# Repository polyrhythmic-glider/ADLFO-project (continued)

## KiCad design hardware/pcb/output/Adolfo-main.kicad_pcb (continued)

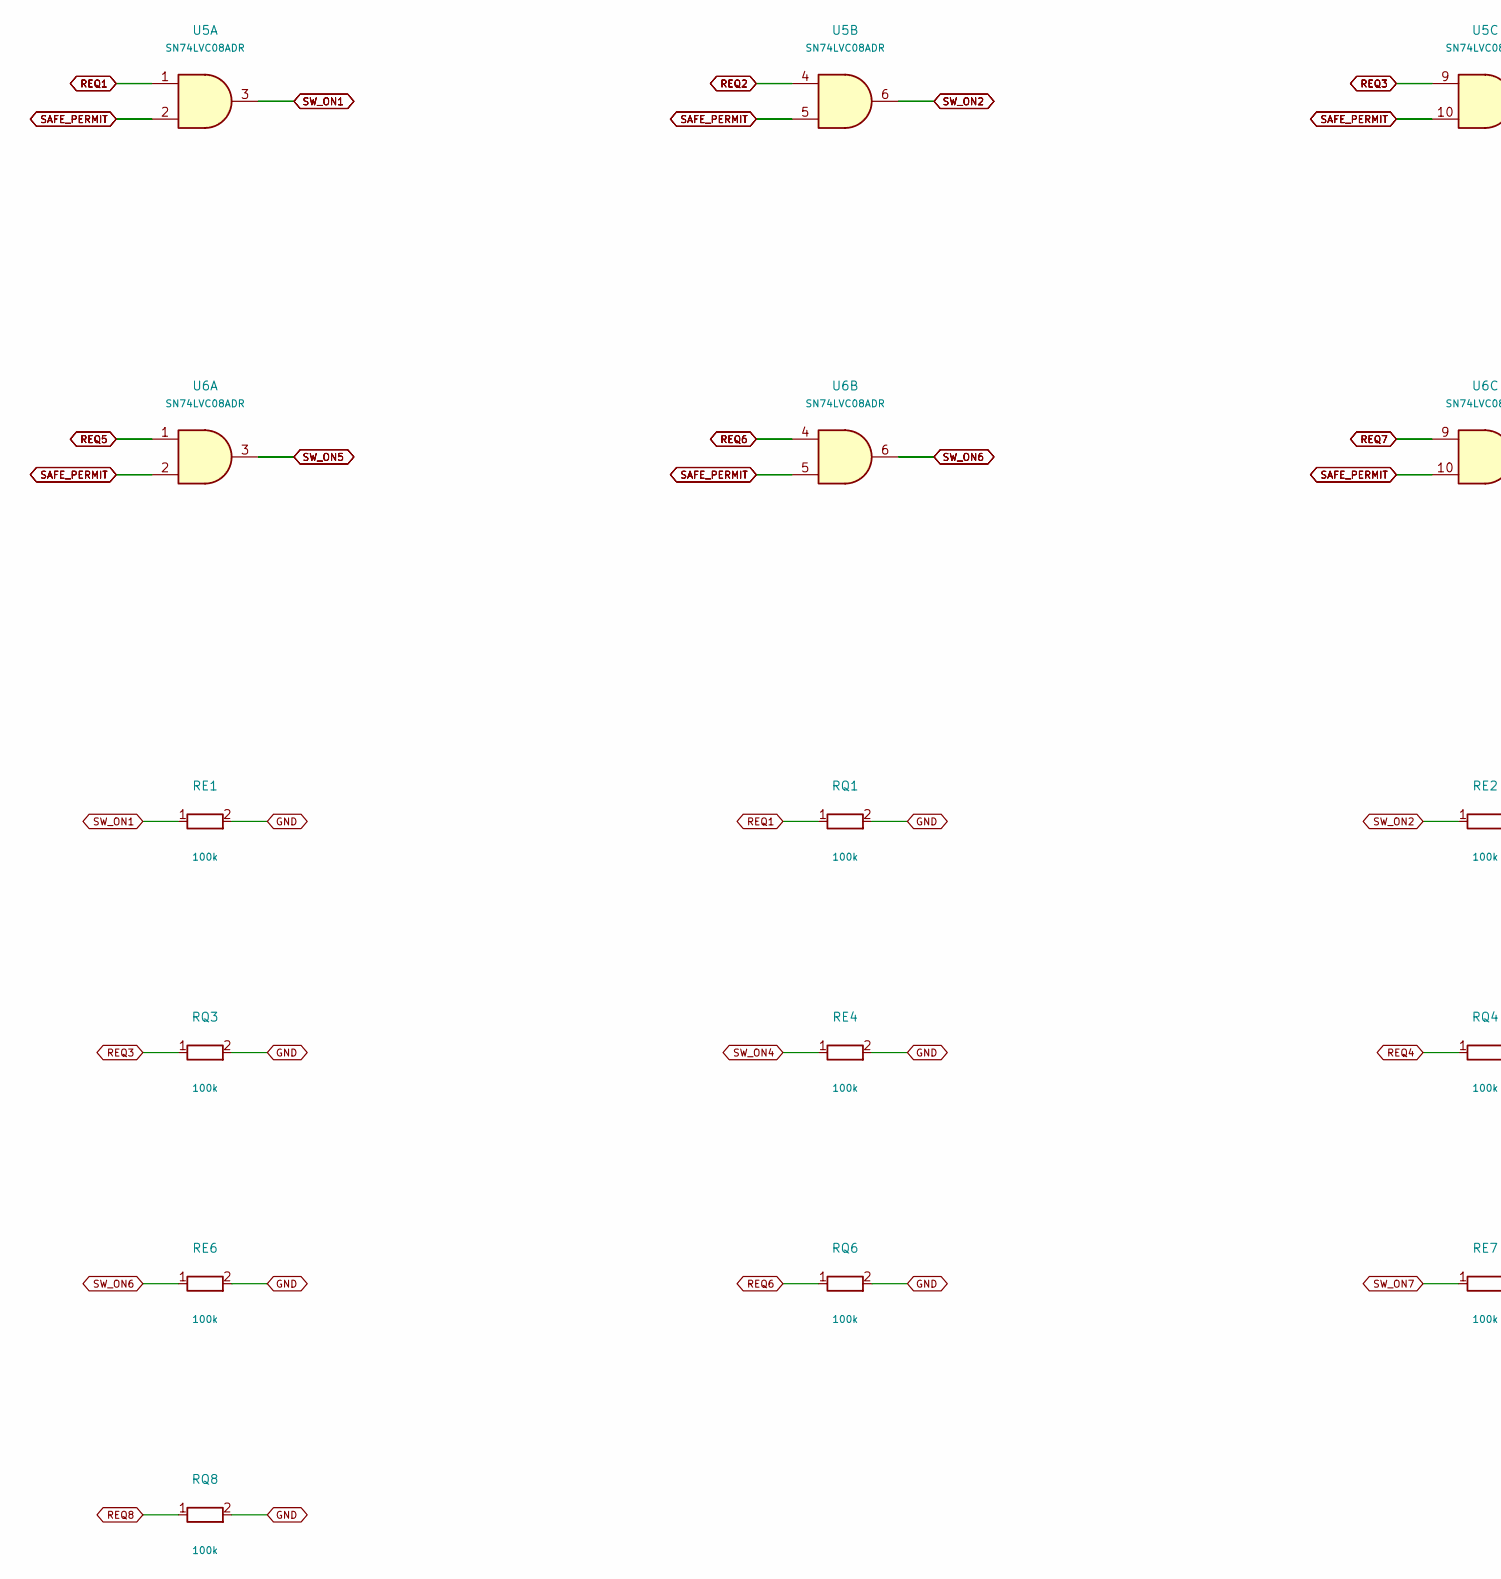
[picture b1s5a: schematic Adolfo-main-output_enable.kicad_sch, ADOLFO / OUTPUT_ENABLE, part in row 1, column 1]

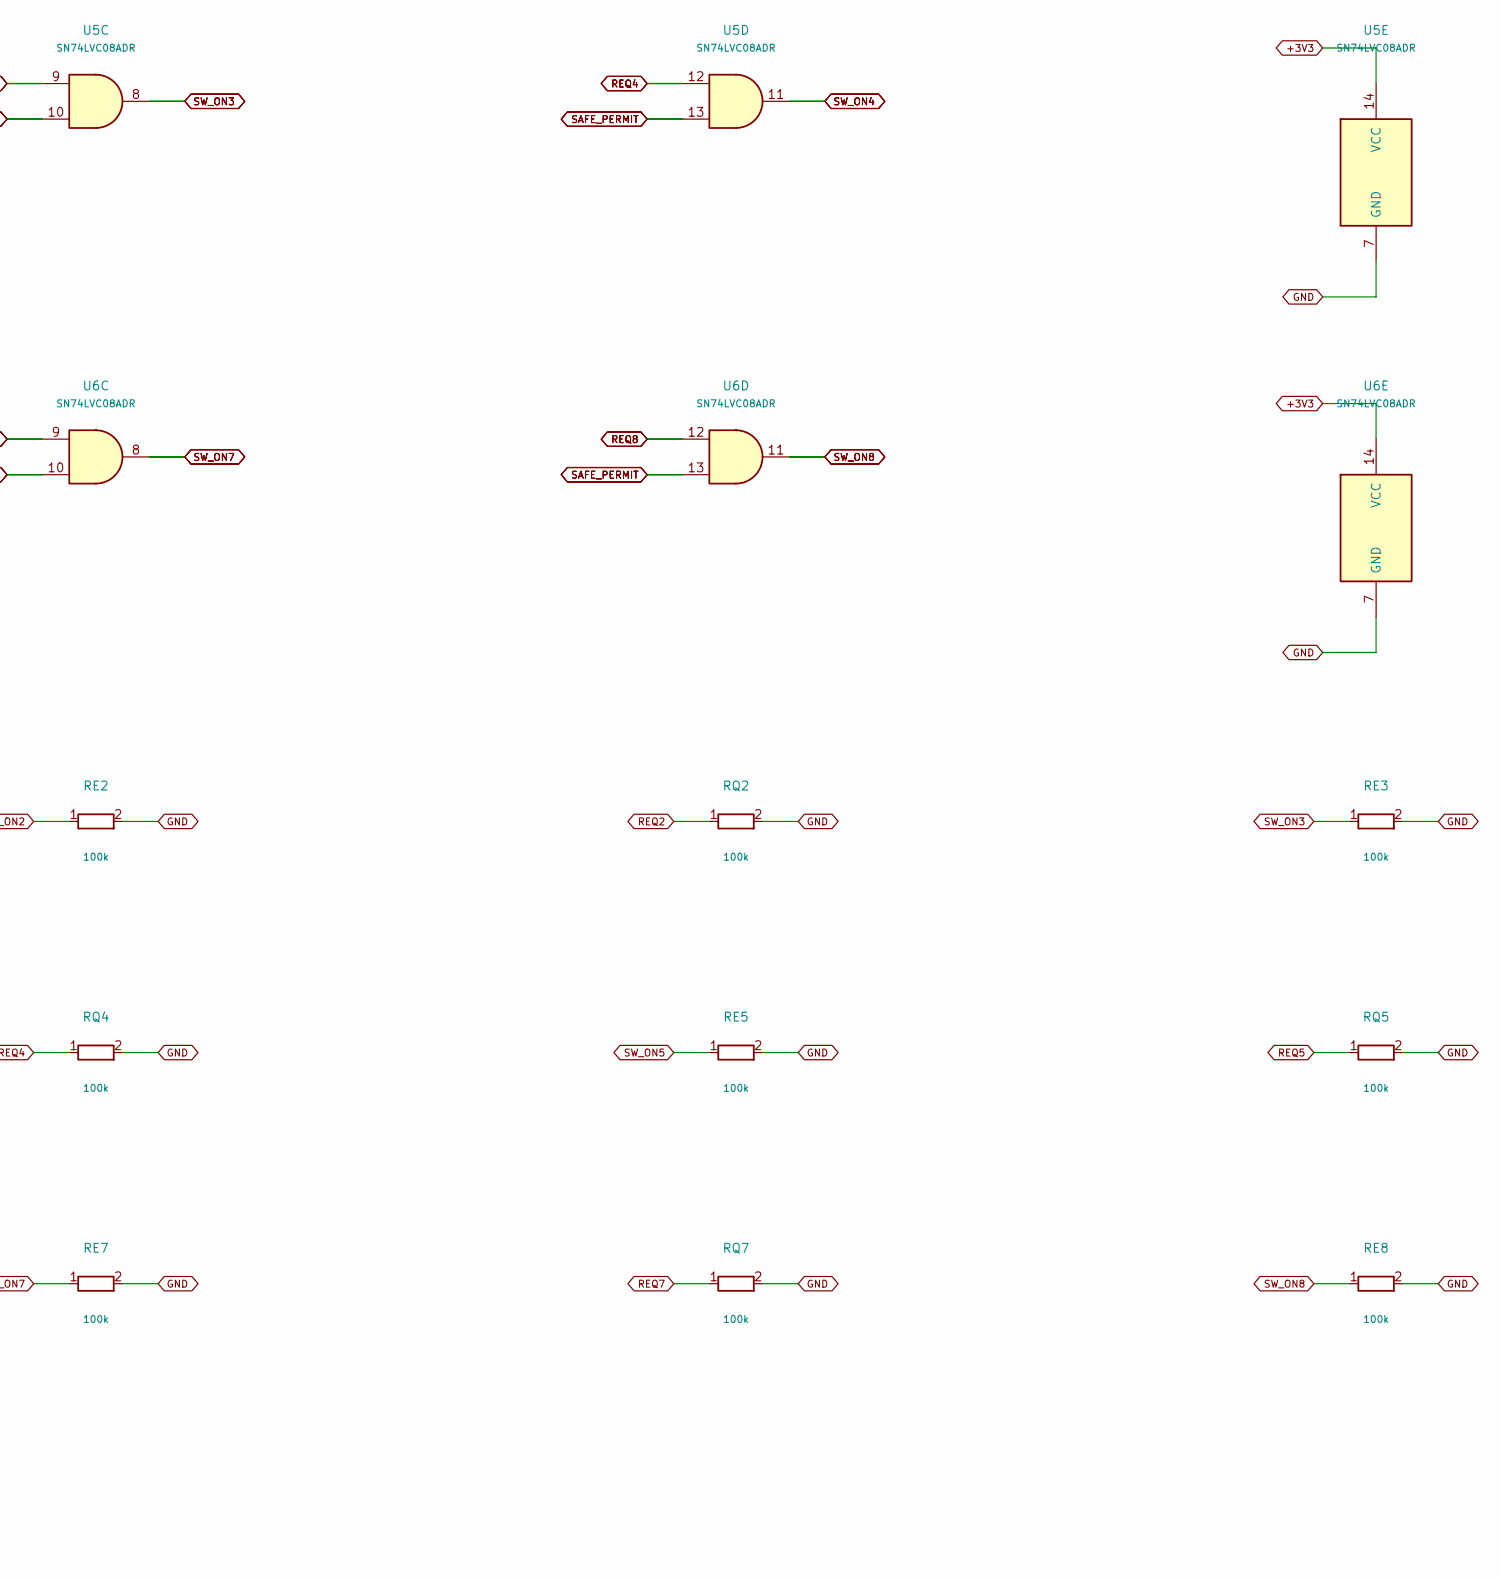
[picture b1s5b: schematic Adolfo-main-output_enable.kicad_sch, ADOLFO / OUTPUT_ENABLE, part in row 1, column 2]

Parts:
RE1, RE2, RE3, RE4, RE5, RE6, RE7, RE8: 100k; r0805
RQ1, RQ2, RQ3, RQ4, RQ5, RQ6, RQ7, RQ8: 100k; r0805
U5, U6: SN74LVC08ADR; soic14; MPN SN74LVC08ADR

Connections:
+3V3: U5.14 (VCC), U6.14 (VCC); also elsewhere on the board
GND: RE1.2, RE2.2, RE3.2, RE4.2, RE5.2, RE6.2, RE7.2, RE8.2, RQ1.2, RQ2.2, RQ3.2, RQ4.2, RQ5.2, RQ6.2, RQ7.2, RQ8.2, U5.7 (GND), U6.7 (GND); also elsewhere on the board
REQ1: RQ1.1, U5.1; also elsewhere on the board
REQ2: RQ2.1, U5.4; also elsewhere on the board
REQ3: RQ3.1, U5.9; also elsewhere on the board
REQ4: RQ4.1, U5.12; also elsewhere on the board
REQ5: RQ5.1, U6.1; also elsewhere on the board
REQ6: RQ6.1, U6.4; also elsewhere on the board
REQ7: RQ7.1, U6.9; also elsewhere on the board
REQ8: RQ8.1, U6.12; also elsewhere on the board
SAFE_PERMIT: U5.2, U5.5, U5.10, U5.13, U6.2, U6.5, U6.10, U6.13; also elsewhere on the board
SW_ON1: RE1.1, U5.3; also elsewhere on the board
SW_ON2: RE2.1, U5.6; also elsewhere on the board
SW_ON3: RE3.1, U5.8; also elsewhere on the board
SW_ON4: RE4.1, U5.11; also elsewhere on the board
SW_ON5: RE5.1, U6.3; also elsewhere on the board
SW_ON6: RE6.1, U6.6; also elsewhere on the board
SW_ON7: RE7.1, U6.8; also elsewhere on the board
SW_ON8: RE8.1, U6.11; also elsewhere on the board

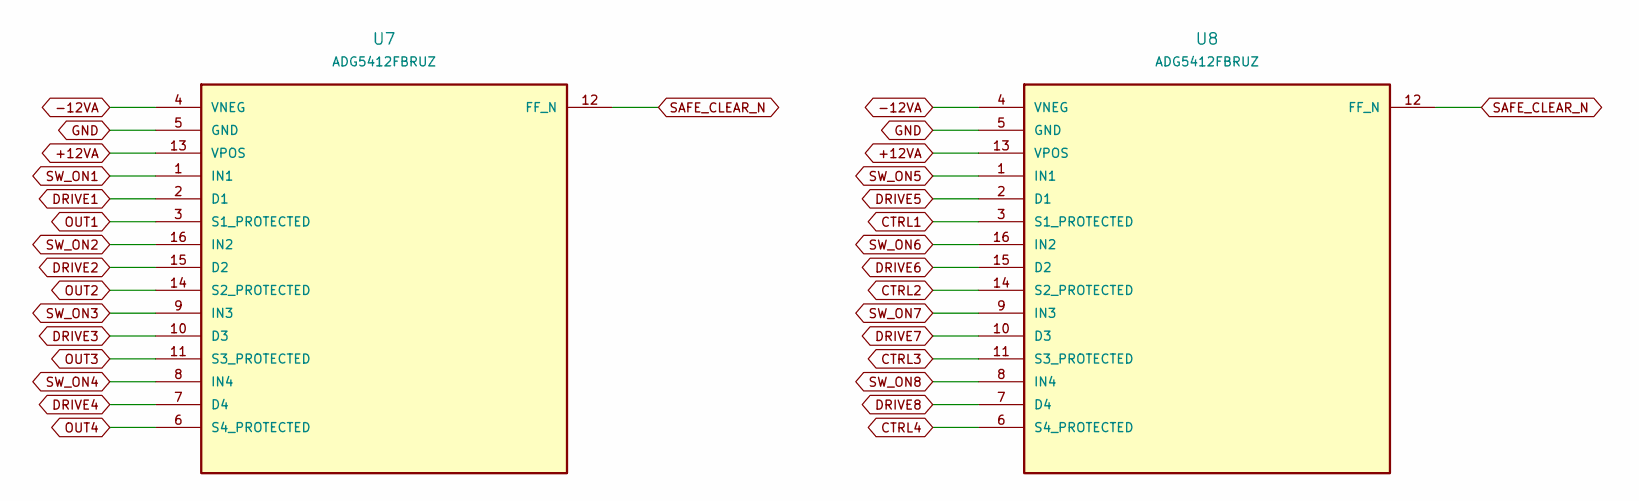
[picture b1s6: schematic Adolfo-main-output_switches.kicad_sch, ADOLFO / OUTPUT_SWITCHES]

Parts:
U7, U8: ADG5412FBRUZ; tssop16; MPN ADG5412FBRUZ

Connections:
+12VA: U7.13 (VPOS), U8.13 (VPOS); also elsewhere on the board
-12VA: U7.4 (VNEG), U8.4 (VNEG); also elsewhere on the board
CTRL1: U8.3 (S1_PROTECTED); also elsewhere on the board
CTRL2: U8.14 (S2_PROTECTED); also elsewhere on the board
CTRL3: U8.11 (S3_PROTECTED); also elsewhere on the board
CTRL4: U8.6 (S4_PROTECTED); also elsewhere on the board
DRIVE1: U7.2 (D1); also elsewhere on the board
DRIVE2: U7.15 (D2); also elsewhere on the board
DRIVE3: U7.10 (D3); also elsewhere on the board
DRIVE4: U7.7 (D4); also elsewhere on the board
DRIVE5: U8.2 (D1); also elsewhere on the board
DRIVE6: U8.15 (D2); also elsewhere on the board
DRIVE7: U8.10 (D3); also elsewhere on the board
DRIVE8: U8.7 (D4); also elsewhere on the board
GND: U7.5 (GND), U8.5 (GND); also elsewhere on the board
OUT1: U7.3 (S1_PROTECTED); also elsewhere on the board
OUT2: U7.14 (S2_PROTECTED); also elsewhere on the board
OUT3: U7.11 (S3_PROTECTED); also elsewhere on the board
OUT4: U7.6 (S4_PROTECTED); also elsewhere on the board
SAFE_CLEAR_N: U7.12 (FF_N), U8.12 (FF_N); also elsewhere on the board
SW_ON1: U7.1 (IN1); also elsewhere on the board
SW_ON2: U7.16 (IN2); also elsewhere on the board
SW_ON3: U7.9 (IN3); also elsewhere on the board
SW_ON4: U7.8 (IN4); also elsewhere on the board
SW_ON5: U8.1 (IN1); also elsewhere on the board
SW_ON6: U8.16 (IN2); also elsewhere on the board
SW_ON7: U8.9 (IN3); also elsewhere on the board
SW_ON8: U8.8 (IN4); also elsewhere on the board

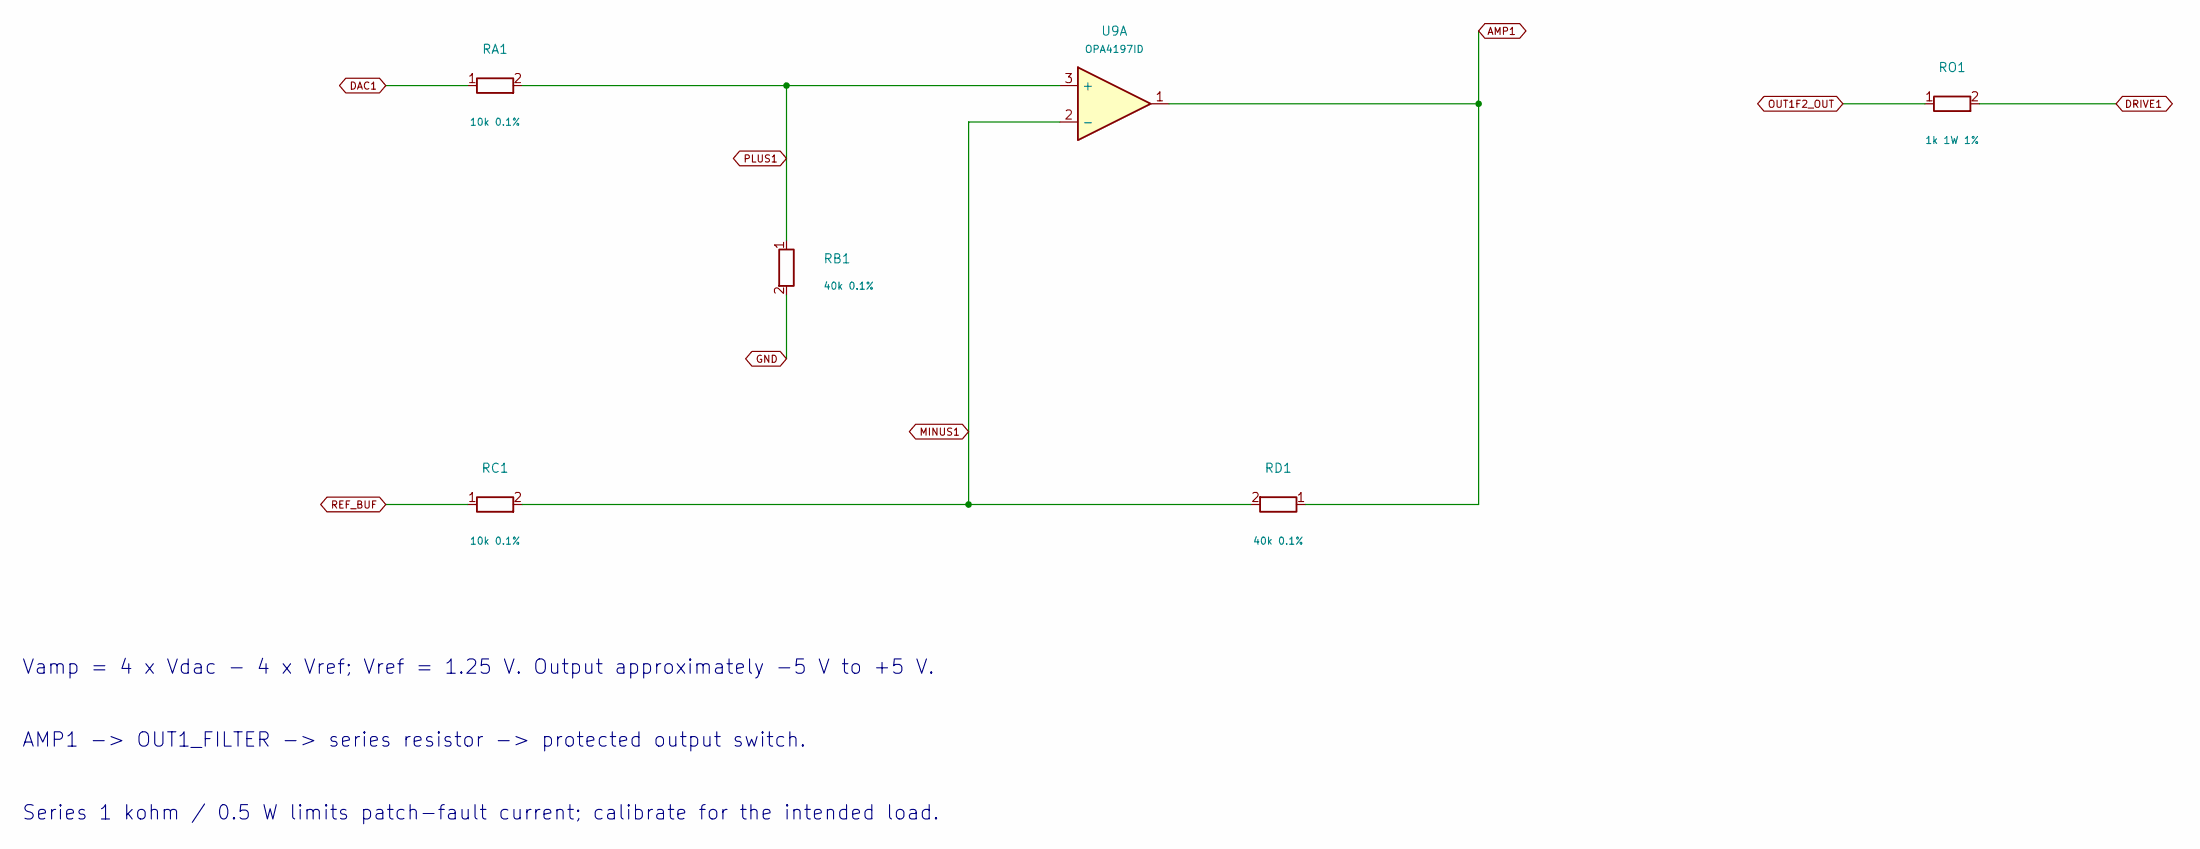
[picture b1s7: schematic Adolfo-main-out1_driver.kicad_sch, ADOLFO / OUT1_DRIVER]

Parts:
RA1: 10k 0.1%; r0805
RB1: 40k 0.1%; r0805
RC1: 10k 0.1%; r0805
RD1: 40k 0.1%; r0805
RO1: 1k 1W 1%; r2010; MPN CRCW20101K00FKEFHP
U9: OPA4197ID; soic14; MPN OPA4197ID

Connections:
AMP1: RD1.1, U9.1; also elsewhere on the board
DAC1: RA1.1; also elsewhere on the board
DRIVE1: RO1.2; also elsewhere on the board
GND: RB1.2; also elsewhere on the board
MINUS1: RC1.2, RD1.2, U9.2 (-)
OUT1F2_OUT: RO1.1; also elsewhere on the board
PLUS1: RA1.2, RB1.1, U9.3 (+)
REF_BUF: RC1.1; also elsewhere on the board

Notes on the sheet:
AMP1 -> OUT1_FILTER -> series resistor -> protected output switch.
Vamp = 4 x Vdac - 4 x Vref; Vref = 1.25 V. Output approximately -5 V to +5 V.
Series 1 kohm / 0.5 W limits patch-fault current; calibrate for the intended load.

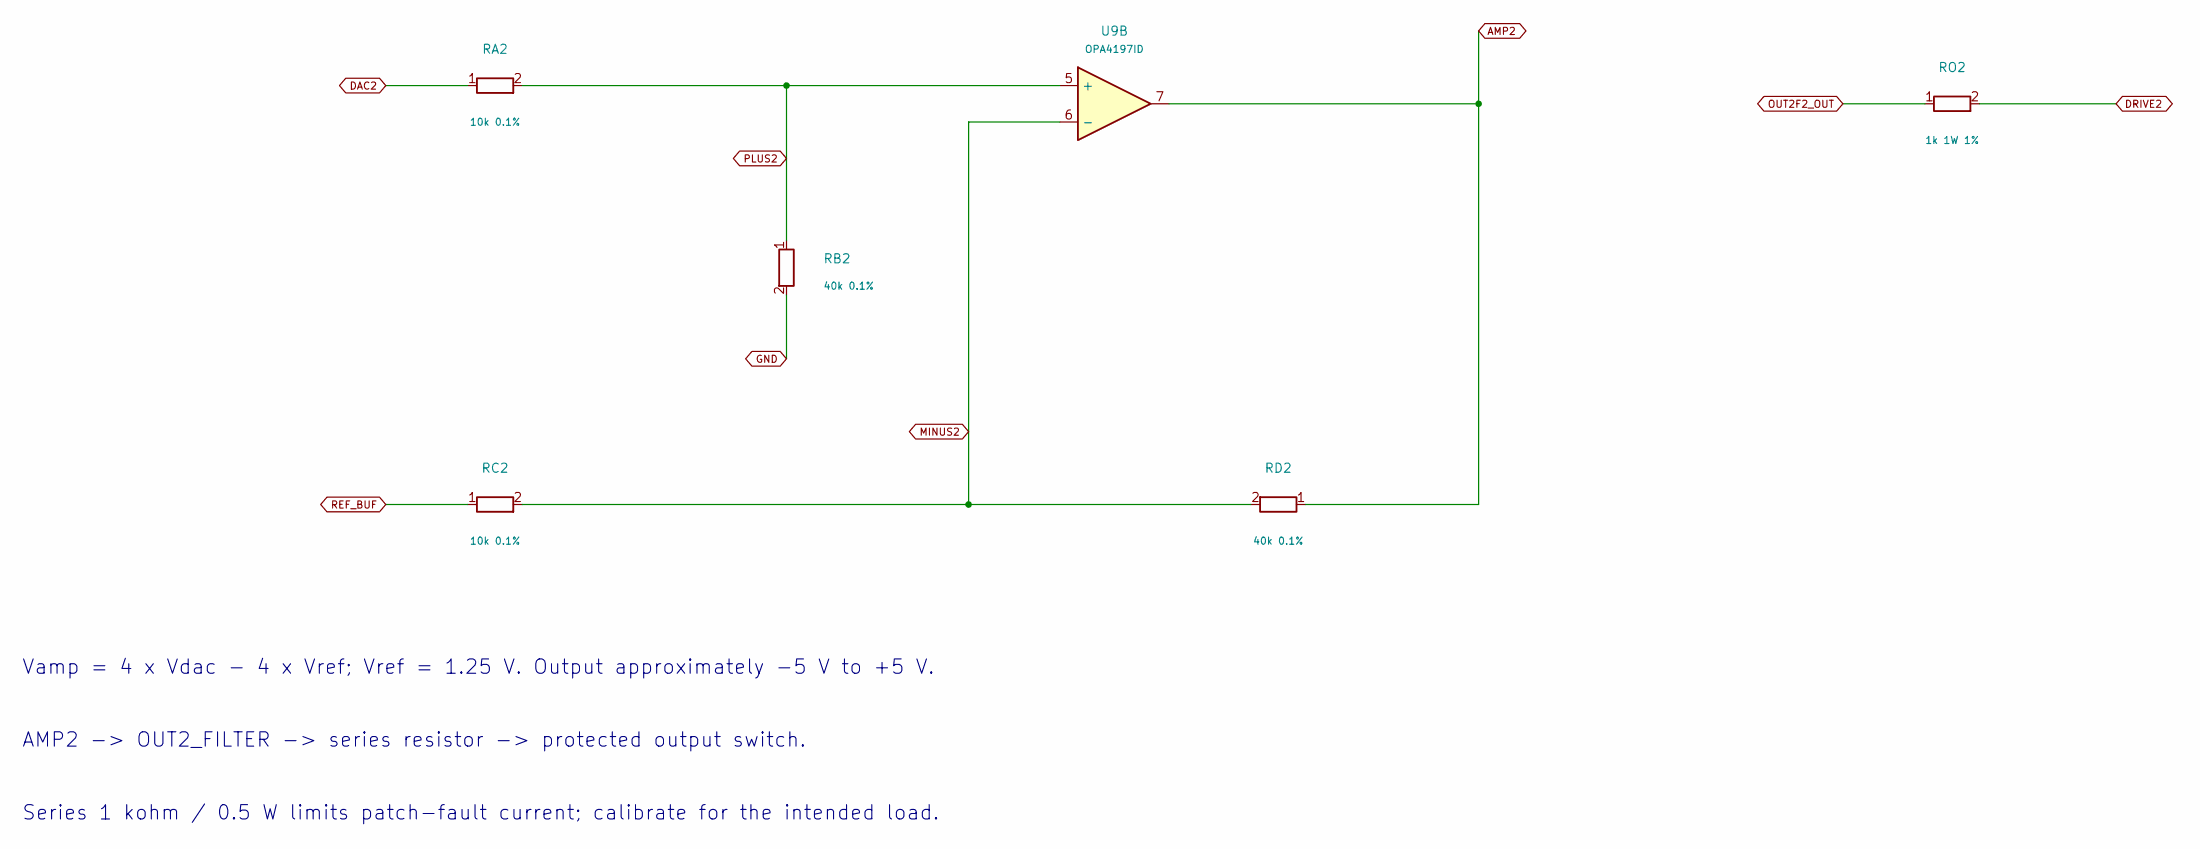
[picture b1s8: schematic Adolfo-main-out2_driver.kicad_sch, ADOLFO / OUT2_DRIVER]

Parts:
RA2: 10k 0.1%; r0805
RB2: 40k 0.1%; r0805
RC2: 10k 0.1%; r0805
RD2: 40k 0.1%; r0805
RO2: 1k 1W 1%; r2010; MPN CRCW20101K00FKEFHP
U9: OPA4197ID; soic14; MPN OPA4197ID

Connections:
AMP2: RD2.1, U9.7; also elsewhere on the board
DAC2: RA2.1; also elsewhere on the board
DRIVE2: RO2.2; also elsewhere on the board
GND: RB2.2; also elsewhere on the board
MINUS2: RC2.2, RD2.2, U9.6 (-)
OUT2F2_OUT: RO2.1; also elsewhere on the board
PLUS2: RA2.2, RB2.1, U9.5 (+)
REF_BUF: RC2.1; also elsewhere on the board

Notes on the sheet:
AMP2 -> OUT2_FILTER -> series resistor -> protected output switch.
Vamp = 4 x Vdac - 4 x Vref; Vref = 1.25 V. Output approximately -5 V to +5 V.
Series 1 kohm / 0.5 W limits patch-fault current; calibrate for the intended load.

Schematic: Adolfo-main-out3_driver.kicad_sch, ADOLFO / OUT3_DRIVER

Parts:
RA3: 10k 0.1%; r0805
RB3: 40k 0.1%; r0805
RC3: 10k 0.1%; r0805
RD3: 40k 0.1%; r0805
RO3: 1k 1W 1%; r2010; MPN CRCW20101K00FKEFHP
U9: OPA4197ID; soic14; MPN OPA4197ID

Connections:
AMP3: RD3.1, U9.8; also elsewhere on the board
DAC3: RA3.1; also elsewhere on the board
DRIVE3: RO3.2; also elsewhere on the board
GND: RB3.2; also elsewhere on the board
MINUS3: RC3.2, RD3.2, U9.9 (-)
OUT3F2_OUT: RO3.1; also elsewhere on the board
PLUS3: RA3.2, RB3.1, U9.10 (+)
REF_BUF: RC3.1; also elsewhere on the board

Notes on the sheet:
AMP3 -> OUT3_FILTER -> series resistor -> protected output switch.
Vamp = 4 x Vdac - 4 x Vref; Vref = 1.25 V. Output approximately -5 V to +5 V.
Series 1 kohm / 0.5 W limits patch-fault current; calibrate for the intended load.

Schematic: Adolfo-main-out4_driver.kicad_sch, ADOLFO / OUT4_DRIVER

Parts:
RA4: 10k 0.1%; r0805
RB4: 40k 0.1%; r0805
RC4: 10k 0.1%; r0805
RD4: 40k 0.1%; r0805
RO4: 1k 1W 1%; r2010; MPN CRCW20101K00FKEFHP
U9: OPA4197ID; soic14; MPN OPA4197ID

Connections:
AMP4: RD4.1, U9.14; also elsewhere on the board
DAC4: RA4.1; also elsewhere on the board
DRIVE4: RO4.2; also elsewhere on the board
GND: RB4.2; also elsewhere on the board
MINUS4: RC4.2, RD4.2, U9.13 (-)
OUT4F2_OUT: RO4.1; also elsewhere on the board
PLUS4: RA4.2, RB4.1, U9.12 (+)
REF_BUF: RC4.1; also elsewhere on the board

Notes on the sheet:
AMP4 -> OUT4_FILTER -> series resistor -> protected output switch.
Vamp = 4 x Vdac - 4 x Vref; Vref = 1.25 V. Output approximately -5 V to +5 V.
Series 1 kohm / 0.5 W limits patch-fault current; calibrate for the intended load.

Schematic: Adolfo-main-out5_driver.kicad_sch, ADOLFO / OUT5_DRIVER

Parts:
RA5: 10k 0.1%; r0805
RB5: 40k 0.1%; r0805
RC5: 10k 0.1%; r0805
RD5: 40k 0.1%; r0805
RO5: 1k 1W 1%; r2010; MPN CRCW20101K00FKEFHP
U10: OPA4197ID; soic14; MPN OPA4197ID

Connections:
AMP5: RD5.1, RO5.1, U10.1
DAC5: RA5.1; also elsewhere on the board
DRIVE5: RO5.2; also elsewhere on the board
GND: RB5.2; also elsewhere on the board
MINUS5: RC5.2, RD5.2, U10.2 (-)
PLUS5: RA5.2, RB5.1, U10.3 (+)
REF_BUF: RC5.1; also elsewhere on the board

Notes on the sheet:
Vamp = 4 x Vdac - 4 x Vref; Vref = 1.25 V. Output approximately -5 V to +5 V.
Series 1 kohm / 0.5 W limits patch-fault current; calibrate for the intended load.

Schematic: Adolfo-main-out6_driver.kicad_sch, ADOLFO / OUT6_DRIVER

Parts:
RA6: 10k 0.1%; r0805
RB6: 40k 0.1%; r0805
RC6: 10k 0.1%; r0805
RD6: 40k 0.1%; r0805
RO6: 1k 1W 1%; r2010; MPN CRCW20101K00FKEFHP
U10: OPA4197ID; soic14; MPN OPA4197ID

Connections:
AMP6: RD6.1, RO6.1, U10.7
DAC6: RA6.1; also elsewhere on the board
DRIVE6: RO6.2; also elsewhere on the board
GND: RB6.2; also elsewhere on the board
MINUS6: RC6.2, RD6.2, U10.6 (-)
PLUS6: RA6.2, RB6.1, U10.5 (+)
REF_BUF: RC6.1; also elsewhere on the board

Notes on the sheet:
Vamp = 4 x Vdac - 4 x Vref; Vref = 1.25 V. Output approximately -5 V to +5 V.
Series 1 kohm / 0.5 W limits patch-fault current; calibrate for the intended load.

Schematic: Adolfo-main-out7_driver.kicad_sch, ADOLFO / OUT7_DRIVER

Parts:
RA7: 10k 0.1%; r0805
RB7: 40k 0.1%; r0805
RC7: 10k 0.1%; r0805
RD7: 40k 0.1%; r0805
RO7: 1k 1W 1%; r2010; MPN CRCW20101K00FKEFHP
U10: OPA4197ID; soic14; MPN OPA4197ID

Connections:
AMP7: RD7.1, RO7.1, U10.8
DAC7: RA7.1; also elsewhere on the board
DRIVE7: RO7.2; also elsewhere on the board
GND: RB7.2; also elsewhere on the board
MINUS7: RC7.2, RD7.2, U10.9 (-)
PLUS7: RA7.2, RB7.1, U10.10 (+)
REF_BUF: RC7.1; also elsewhere on the board

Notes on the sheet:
Vamp = 4 x Vdac - 4 x Vref; Vref = 1.25 V. Output approximately -5 V to +5 V.
Series 1 kohm / 0.5 W limits patch-fault current; calibrate for the intended load.

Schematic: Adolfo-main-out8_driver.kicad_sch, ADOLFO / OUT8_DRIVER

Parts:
RA8: 10k 0.1%; r0805
RB8: 40k 0.1%; r0805
RC8: 10k 0.1%; r0805
RD8: 40k 0.1%; r0805
RO8: 1k 1W 1%; r2010; MPN CRCW20101K00FKEFHP
U10: OPA4197ID; soic14; MPN OPA4197ID

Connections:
AMP8: RD8.1, RO8.1, U10.14
DAC8: RA8.1; also elsewhere on the board
DRIVE8: RO8.2; also elsewhere on the board
GND: RB8.2; also elsewhere on the board
MINUS8: RC8.2, RD8.2, U10.13 (-)
PLUS8: RA8.2, RB8.1, U10.12 (+)
REF_BUF: RC8.1; also elsewhere on the board

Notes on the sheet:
Vamp = 4 x Vdac - 4 x Vref; Vref = 1.25 V. Output approximately -5 V to +5 V.
Series 1 kohm / 0.5 W limits patch-fault current; calibrate for the intended load.

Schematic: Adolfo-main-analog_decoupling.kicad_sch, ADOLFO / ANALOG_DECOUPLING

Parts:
U9, U10, U11, U21, U22, U23, U24: OPA4197ID; soic14; MPN OPA4197ID

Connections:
+12VA: U9.4 (V+), U10.4 (V+), U11.4 (V+), U21.4 (V+), U22.4 (V+), U23.4 (V+), U24.4 (V+); also elsewhere on the board
-12VA: U9.11 (V-), U10.11 (V-), U11.11 (V-), U21.11 (V-), U22.11 (V-), U23.11 (V-), U24.11 (V-); also elsewhere on the board

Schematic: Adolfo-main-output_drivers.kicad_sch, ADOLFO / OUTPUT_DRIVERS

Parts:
C1, C2, C3, C4, C5, C6: 100nF 50V; c0805

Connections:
+12VA: C1.1, C3.1, C5.1; also elsewhere on the board
-12VA: C2.1, C4.1, C6.1; also elsewhere on the board
GND: C1.2, C2.2, C3.2, C4.2, C5.2, C6.2; also elsewhere on the board

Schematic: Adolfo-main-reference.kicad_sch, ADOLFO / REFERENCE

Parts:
RREF1, RREF2: 10k 0.1%; r0805
U11: OPA4197ID; soic14; MPN OPA4197ID

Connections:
GND: RREF2.2, U11.5 (+), U11.10 (+), U11.12 (+); also elsewhere on the board
REF2V5: RREF1.1; also elsewhere on the board
REF_BUF: U11.1, U11.2 (-); also elsewhere on the board
REF_HALF: RREF1.2, RREF2.1, U11.3 (+)
UNUSED_FB7: U11.6 (-), U11.7
UNUSED_FB8: U11.8, U11.9 (-)
UNUSED_FB14: U11.13 (-), U11.14

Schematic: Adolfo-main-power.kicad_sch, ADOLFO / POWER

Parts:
C7: 47uF 10V; c0805
C8: 10uF 10V; c0805
C60, C61: 22uF 25V X7R; c1210
C62: 100nF 50V; c0805
C63: 100nF; c0805
CD1, CD2, CD3, CD4, CD5, CD6, CD7, CD8, CD9: 100nF; c0805
CI1, CI2, CI3, CI4: 100pF C0G; c0805
CI5, CI6, CI7, CI8: 1nF C0G; c0805
D1, D2: SS14; sma
F1: Littelfuse 1206L075/24YR; fuse1206
F2: Littelfuse 1206L025/30YR; fuse1206
FB1: BLM21PG601SN1D; r0805
J16: Wurth 61201021621 IDC10; idc10
RI1, RI2, RI3, RI4, RI5, RI6, RI7, RI8: 1k 1W 1%; r2010; MPN CRCW20101K00FKEFHP
TP1: GND; testpoint
TP2: +12VA; testpoint
TP3: -12VA; testpoint
TP4: +5D; testpoint
TP5: +5A; testpoint
TP6: REF_BUF; testpoint
U25: R-78E5.0-1.0; recom; MPN R-78E5.0-1.0

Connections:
+3V3: CD3.1, CD4.1, CD5.1; also elsewhere on the board
+5A: C8.1, CD2.1, FB1.2, TP5.1; also elsewhere on the board
+5D: C7.1, C63.1, CD1.1, FB1.1, TP4.1, U25.3 (OUT); also elsewhere on the board
+12VA: C60.1, C62.1, CD6.1, CD8.1, D1.1 (K), TP2.1, U25.1 (IN); also elsewhere on the board
+12_FUSED: D1.2 (A), F1.2
+12_IN: F1.1, J16.9, J16.10
-12VA: C61.1, CD7.1, CD9.1, D2.2 (A), TP3.1; also elsewhere on the board
-12_FUSED: D2.1 (K), F2.2
-12_IN: F2.1, J16.1, J16.2
ADC_IN1: CI1.1; also elsewhere on the board
ADC_IN2: CI2.1; also elsewhere on the board
ADC_IN3: CI3.1; also elsewhere on the board
ADC_IN4: CI4.1; also elsewhere on the board
ADC_IN5: CI5.1; also elsewhere on the board
ADC_IN6: CI6.1; also elsewhere on the board
ADC_IN7: CI7.1; also elsewhere on the board
ADC_IN8: CI8.1; also elsewhere on the board
CTRL1: RI5.1; also elsewhere on the board
CTRL2: RI6.1; also elsewhere on the board
CTRL3: RI7.1; also elsewhere on the board
CTRL4: RI8.1; also elsewhere on the board
GND: C7.2, C8.2, C60.2, C61.2, C62.2, C63.2, CD1.2, CD2.2, CD3.2, CD4.2, CD5.2, CD6.2, CD7.2, CD8.2, CD9.2, CI1.2, CI2.2, CI3.2, CI4.2, CI5.2, CI6.2, CI7.2, CI8.2, J16.3, J16.4, J16.5, J16.6, J16.7, J16.8, TP1.1, U25.2 (GND); also elsewhere on the board
IN1: RI1.1; also elsewhere on the board
IN2: RI2.1; also elsewhere on the board
IN3: RI3.1; also elsewhere on the board
IN4: RI4.1; also elsewhere on the board
INPUT_LIMIT1: RI1.2; also elsewhere on the board
INPUT_LIMIT2: RI2.2; also elsewhere on the board
INPUT_LIMIT3: RI3.2; also elsewhere on the board
INPUT_LIMIT4: RI4.2; also elsewhere on the board
INPUT_LIMIT5: RI5.2; also elsewhere on the board
INPUT_LIMIT6: RI6.2; also elsewhere on the board
INPUT_LIMIT7: RI7.2; also elsewhere on the board
INPUT_LIMIT8: RI8.2; also elsewhere on the board
REF_BUF: TP6.1; also elsewhere on the board

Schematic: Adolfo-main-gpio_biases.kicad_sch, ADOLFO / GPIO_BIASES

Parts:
R1: 10k; r0805
R2, R3: 2.2k; r0805
RP1, RP2, RP3, RP4, RP5, RP6, RP7, RP8: 10k; r0805
RU1, RU2, RU3, RU4, RU5: 10k; r0805

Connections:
+3V3: R2.2, R3.2, RP1.2, RP2.2, RP3.2, RP4.2, RP5.2, RP6.2, RP7.2, RP8.2, RU1.2, RU2.2, RU3.2, RU4.2, RU5.2; also elsewhere on the board
ADC_CS: RU1.1; also elsewhere on the board
DAC_CLR: RU4.1; also elsewhere on the board
DAC_LDAC: RU3.1; also elsewhere on the board
DAC_SYNC: RU2.1; also elsewhere on the board
ENC1_A: RP1.1; also elsewhere on the board
ENC1_B: RP2.1; also elsewhere on the board
ENC2_A: RP3.1; also elsewhere on the board
ENC2_B: RP4.1; also elsewhere on the board
ENC3_A: RP5.1; also elsewhere on the board
ENC3_B: RP6.1; also elsewhere on the board
ENC4_A: RP7.1; also elsewhere on the board
ENC4_B: RP8.1; also elsewhere on the board
GND: R1.2; also elsewhere on the board
I2C_SCL: R2.1; also elsewhere on the board
I2C_SDA: R3.1; also elsewhere on the board
IO_RESET: RU5.1; also elsewhere on the board
OUTPUT_PERMIT: R1.1; also elsewhere on the board

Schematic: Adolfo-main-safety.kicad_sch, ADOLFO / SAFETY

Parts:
C13, C15: 10nF; c0805
C14: 1nF; c0805
CMON5: 10nF; c0805
CSAFE16, CSAFE17, CSAFE18, CSAFE19, CSAFE20: 100nF; c0805
D3: BAT54WS; sod323
R4: 0R; r0805
R5, R6: 10k; r0805
R7: 109k 0.1%; r0805
R8: 10k 0.1%; r0805
RMONREF1, RMONREF2: 10k 0.1%; r0805
RNMON1: 1M 0.1%; r0805
RNMON2: 137k 0.1%; r0805
RPMON1: 53.1k 0.1%; r0805
RPMON2: 10k 0.1%; r0805
U16: SN74HCS74DR; soic14; MPN SN74HCS74DR
U17: TPS3828-33DBVR; sot23_5; MPN TPS3828-33DBVR
U18: TPS3808G01DBVR; sot23_6; MPN TPS3808G01DBVR
U19: LM393BDR; soic8; MPN LM393BDR
U20: SN74LVC1G08DBVR; sot23_5; MPN SN74LVC1G08DBVR

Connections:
+3V3: CSAFE16.1, CSAFE17.1, CSAFE18.1, CSAFE20.1, R5.2, RMONREF1.1, RNMON2.1, U16.2 (D), U16.4 (~S), U16.10 (~S), U16.14 (VCC), U17.3 (MR_N), U17.5 (VDD), U18.3 (MR_N), U18.6 (VDD), U20.5 (VCC); also elsewhere on the board
+5A: CSAFE19.1, R7.1, U19.8 (V+); also elsewhere on the board
+12VA: RPMON1.1; also elsewhere on the board
-12VA: RNMON1.1; also elsewhere on the board
FAULT_N: R4.2; also elsewhere on the board
GND: C13.2, C14.2, C15.2, CMON5.2, CSAFE16.2, CSAFE17.2, CSAFE18.2, CSAFE19.2, CSAFE20.2, D3.2 (A), R6.2, R8.2, RMONREF2.2, RPMON2.2, U16.7 (GND), U16.11 (C), U16.12 (D), U16.13 (~R), U17.2 (GND), U18.2 (GND), U19.4 (V-), U20.3 (GND); also elsewhere on the board
OUTPUT_PERMIT: U16.3 (C), U20.2; also elsewhere on the board
REF_MON: RMONREF1.2, RMONREF2.1, U19.2 (-), U19.5 (+)
RESET_DELAY: C15.1, U18.4 (CT)
SAFE_CLEAR_N: R4.1, R5.1, U16.1 (~R), U17.1 (RESET_N), U18.1 (RESET_N), U19.1, U19.7; also elsewhere on the board
SAFE_LATCH: U16.5 (Q), U20.1
SAFE_PERMIT: U20.4; also elsewhere on the board
SENSE_5A: CMON5.1, R7.2, R8.1, U18.5 (SENSE)
SENSE_NEG: C14.1, D3.1 (K), RNMON1.2, RNMON2.2, U19.6 (-)
SENSE_POS: C13.1, RPMON1.2, RPMON2.1, U19.3 (+)
WATCHDOG: R6.1, U17.4 (WDI); also elsewhere on the board

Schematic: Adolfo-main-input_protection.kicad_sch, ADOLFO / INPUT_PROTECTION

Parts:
C16, C17, C18, C19: 100nF 50V; c0805
U14, U15: ADG5412FBRUZ; tssop16; MPN ADG5412FBRUZ

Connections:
+3V3: U14.1 (IN1), U14.8 (IN4), U14.9 (IN3), U14.16 (IN2), U15.1 (IN1), U15.8 (IN4), U15.9 (IN3), U15.16 (IN2); also elsewhere on the board
+12VA: C16.1, C18.1, U14.13 (VPOS), U15.13 (VPOS); also elsewhere on the board
-12VA: C17.1, C19.1, U14.4 (VNEG), U15.4 (VNEG); also elsewhere on the board
GND: C16.2, C17.2, C18.2, C19.2, U14.5 (GND), U15.5 (GND); also elsewhere on the board
INPUT_LIMIT1: U14.3 (S1_PROTECTED); also elsewhere on the board
INPUT_LIMIT2: U14.14 (S2_PROTECTED); also elsewhere on the board
INPUT_LIMIT3: U14.11 (S3_PROTECTED); also elsewhere on the board
INPUT_LIMIT4: U14.6 (S4_PROTECTED); also elsewhere on the board
INPUT_LIMIT5: U15.3 (S1_PROTECTED); also elsewhere on the board
INPUT_LIMIT6: U15.14 (S2_PROTECTED); also elsewhere on the board
INPUT_LIMIT7: U15.11 (S3_PROTECTED); also elsewhere on the board
INPUT_LIMIT8: U15.6 (S4_PROTECTED); also elsewhere on the board
PROTECTED1: U14.2 (D1); also elsewhere on the board
PROTECTED2: U14.15 (D2); also elsewhere on the board
PROTECTED3: U14.10 (D3); also elsewhere on the board
PROTECTED4: U14.7 (D4); also elsewhere on the board
PROTECTED5: U15.2 (D1); also elsewhere on the board
PROTECTED6: U15.15 (D2); also elsewhere on the board
PROTECTED7: U15.10 (D3); also elsewhere on the board
PROTECTED8: U15.7 (D4); also elsewhere on the board
SAFE_CLEAR_N: U14.12 (FF_N), U15.12 (FF_N); also elsewhere on the board

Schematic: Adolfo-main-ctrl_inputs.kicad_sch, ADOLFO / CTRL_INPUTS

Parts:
RIC5, RIC6, RIC7, RIC8: 1k; r0805

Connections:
ADC_IN5: RIC5.2; also elsewhere on the board
ADC_IN6: RIC6.2; also elsewhere on the board
ADC_IN7: RIC7.2; also elsewhere on the board
ADC_IN8: RIC8.2; also elsewhere on the board
PROTECTED5: RIC5.1; also elsewhere on the board
PROTECTED6: RIC6.1; also elsewhere on the board
PROTECTED7: RIC7.1; also elsewhere on the board
PROTECTED8: RIC8.1; also elsewhere on the board

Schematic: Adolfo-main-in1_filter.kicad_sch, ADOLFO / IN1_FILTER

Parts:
C20: 820pF C0G 1%; c0805
C21: 680pF C0G 1%; c0805
C22: 1.8nF C0G 1%; c0805
C23: 270pF C0G 1%; c0805
R9, R10, R11, R12: 11k 0.1%; r0805
RADCF1: 47R; r0805
U21: OPA4197ID; soic14; MPN OPA4197ID

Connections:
ADC_IN1: RADCF1.2; also elsewhere on the board
GND: C21.2, C23.2; also elsewhere on the board
IN1F1_A: C20.1, R9.2, R10.1
IN1F1_B: C21.1, R10.2, U21.3 (+)
IN1F1_OUT: C20.2, R11.1, U21.1, U21.2 (-)
IN1F2_A: C22.1, R11.2, R12.1
IN1F2_B: C23.1, R12.2, U21.5 (+)
IN1F2_OUT: C22.2, RADCF1.1, U21.6 (-), U21.7
PROTECTED1: R9.1; also elsewhere on the board

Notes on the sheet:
IN1: unity-gain, DC-coupled fourth-order low-pass, approximately 20 kHz.
C0G capacitors 1%, resistors 0.1%. Op-amp supply units: ANALOG_DECOUPLING.

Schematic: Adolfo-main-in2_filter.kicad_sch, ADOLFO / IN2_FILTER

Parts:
C24: 820pF C0G 1%; c0805
C25: 680pF C0G 1%; c0805
C26: 1.8nF C0G 1%; c0805
C27: 270pF C0G 1%; c0805
R13, R14, R15, R16: 11k 0.1%; r0805
RADCF2: 47R; r0805
U21: OPA4197ID; soic14; MPN OPA4197ID

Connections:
ADC_IN2: RADCF2.2; also elsewhere on the board
GND: C25.2, C27.2; also elsewhere on the board
IN2F1_A: C24.1, R13.2, R14.1
IN2F1_B: C25.1, R14.2, U21.10 (+)
IN2F1_OUT: C24.2, R15.1, U21.8, U21.9 (-)
IN2F2_A: C26.1, R15.2, R16.1
IN2F2_B: C27.1, R16.2, U21.12 (+)
IN2F2_OUT: C26.2, RADCF2.1, U21.13 (-), U21.14
PROTECTED2: R13.1; also elsewhere on the board

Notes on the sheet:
IN2: unity-gain, DC-coupled fourth-order low-pass, approximately 20 kHz.
C0G capacitors 1%, resistors 0.1%. Op-amp supply units: ANALOG_DECOUPLING.

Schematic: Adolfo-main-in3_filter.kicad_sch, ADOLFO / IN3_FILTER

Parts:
C28: 820pF C0G 1%; c0805
C29: 680pF C0G 1%; c0805
C30: 1.8nF C0G 1%; c0805
C31: 270pF C0G 1%; c0805
R17, R18, R19, R20: 11k 0.1%; r0805
RADCF3: 47R; r0805
U22: OPA4197ID; soic14; MPN OPA4197ID

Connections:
ADC_IN3: RADCF3.2; also elsewhere on the board
GND: C29.2, C31.2; also elsewhere on the board
IN3F1_A: C28.1, R17.2, R18.1
IN3F1_B: C29.1, R18.2, U22.3 (+)
IN3F1_OUT: C28.2, R19.1, U22.1, U22.2 (-)
IN3F2_A: C30.1, R19.2, R20.1
IN3F2_B: C31.1, R20.2, U22.5 (+)
IN3F2_OUT: C30.2, RADCF3.1, U22.6 (-), U22.7
PROTECTED3: R17.1; also elsewhere on the board

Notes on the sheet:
IN3: unity-gain, DC-coupled fourth-order low-pass, approximately 20 kHz.
C0G capacitors 1%, resistors 0.1%. Op-amp supply units: ANALOG_DECOUPLING.

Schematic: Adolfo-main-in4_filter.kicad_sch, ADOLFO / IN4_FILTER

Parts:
C32: 820pF C0G 1%; c0805
C33: 680pF C0G 1%; c0805
C34: 1.8nF C0G 1%; c0805
C35: 270pF C0G 1%; c0805
R21, R22, R23, R24: 11k 0.1%; r0805
RADCF4: 47R; r0805
U22: OPA4197ID; soic14; MPN OPA4197ID

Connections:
ADC_IN4: RADCF4.2; also elsewhere on the board
GND: C33.2, C35.2; also elsewhere on the board
IN4F1_A: C32.1, R21.2, R22.1
IN4F1_B: C33.1, R22.2, U22.10 (+)
IN4F1_OUT: C32.2, R23.1, U22.8, U22.9 (-)
IN4F2_A: C34.1, R23.2, R24.1
IN4F2_B: C35.1, R24.2, U22.12 (+)
IN4F2_OUT: C34.2, RADCF4.1, U22.13 (-), U22.14
PROTECTED4: R21.1; also elsewhere on the board

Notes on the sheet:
IN4: unity-gain, DC-coupled fourth-order low-pass, approximately 20 kHz.
C0G capacitors 1%, resistors 0.1%. Op-amp supply units: ANALOG_DECOUPLING.

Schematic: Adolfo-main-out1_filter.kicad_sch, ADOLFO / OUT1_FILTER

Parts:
C36: 820pF C0G 1%; c0805
C37: 680pF C0G 1%; c0805
C38: 1.8nF C0G 1%; c0805
C39: 270pF C0G 1%; c0805
R25, R26, R27, R28: 11k 0.1%; r0805
U23: OPA4197ID; soic14; MPN OPA4197ID

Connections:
AMP1: R25.1; also elsewhere on the board
GND: C37.2, C39.2; also elsewhere on the board
OUT1F1_A: C36.1, R25.2, R26.1
OUT1F1_B: C37.1, R26.2, U23.3 (+)
OUT1F1_OUT: C36.2, R27.1, U23.1, U23.2 (-)
OUT1F2_A: C38.1, R27.2, R28.1
OUT1F2_B: C39.1, R28.2, U23.5 (+)
OUT1F2_OUT: C38.2, U23.6 (-), U23.7; also elsewhere on the board

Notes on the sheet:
OUT1: unity-gain, DC-coupled fourth-order low-pass, approximately 20 kHz.
C0G capacitors 1%, resistors 0.1%. Op-amp supply units: ANALOG_DECOUPLING.

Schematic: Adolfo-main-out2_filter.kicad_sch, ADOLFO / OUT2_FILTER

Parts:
C40: 820pF C0G 1%; c0805
C41: 680pF C0G 1%; c0805
C42: 1.8nF C0G 1%; c0805
C43: 270pF C0G 1%; c0805
R29, R30, R31, R32: 11k 0.1%; r0805
U23: OPA4197ID; soic14; MPN OPA4197ID

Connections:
AMP2: R29.1; also elsewhere on the board
GND: C41.2, C43.2; also elsewhere on the board
OUT2F1_A: C40.1, R29.2, R30.1
OUT2F1_B: C41.1, R30.2, U23.10 (+)
OUT2F1_OUT: C40.2, R31.1, U23.8, U23.9 (-)
OUT2F2_A: C42.1, R31.2, R32.1
OUT2F2_B: C43.1, R32.2, U23.12 (+)
OUT2F2_OUT: C42.2, U23.13 (-), U23.14; also elsewhere on the board

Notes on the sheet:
OUT2: unity-gain, DC-coupled fourth-order low-pass, approximately 20 kHz.
C0G capacitors 1%, resistors 0.1%. Op-amp supply units: ANALOG_DECOUPLING.

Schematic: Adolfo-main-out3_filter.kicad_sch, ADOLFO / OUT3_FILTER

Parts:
C44: 820pF C0G 1%; c0805
C45: 680pF C0G 1%; c0805
C46: 1.8nF C0G 1%; c0805
C47: 270pF C0G 1%; c0805
R33, R34, R35, R36: 11k 0.1%; r0805
U24: OPA4197ID; soic14; MPN OPA4197ID

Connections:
AMP3: R33.1; also elsewhere on the board
GND: C45.2, C47.2; also elsewhere on the board
OUT3F1_A: C44.1, R33.2, R34.1
OUT3F1_B: C45.1, R34.2, U24.3 (+)
OUT3F1_OUT: C44.2, R35.1, U24.1, U24.2 (-)
OUT3F2_A: C46.1, R35.2, R36.1
OUT3F2_B: C47.1, R36.2, U24.5 (+)
OUT3F2_OUT: C46.2, U24.6 (-), U24.7; also elsewhere on the board

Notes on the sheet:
OUT3: unity-gain, DC-coupled fourth-order low-pass, approximately 20 kHz.
C0G capacitors 1%, resistors 0.1%. Op-amp supply units: ANALOG_DECOUPLING.

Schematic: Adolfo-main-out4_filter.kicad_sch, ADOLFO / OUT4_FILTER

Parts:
C48: 820pF C0G 1%; c0805
C49: 680pF C0G 1%; c0805
C50: 1.8nF C0G 1%; c0805
C51: 270pF C0G 1%; c0805
R37, R38, R39, R40: 11k 0.1%; r0805
U24: OPA4197ID; soic14; MPN OPA4197ID

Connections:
AMP4: R37.1; also elsewhere on the board
GND: C49.2, C51.2; also elsewhere on the board
OUT4F1_A: C48.1, R37.2, R38.1
OUT4F1_B: C49.1, R38.2, U24.10 (+)
OUT4F1_OUT: C48.2, R39.1, U24.8, U24.9 (-)
OUT4F2_A: C50.1, R39.2, R40.1
OUT4F2_B: C51.1, R40.2, U24.12 (+)
OUT4F2_OUT: C50.2, U24.13 (-), U24.14; also elsewhere on the board

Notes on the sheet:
OUT4: unity-gain, DC-coupled fourth-order low-pass, approximately 20 kHz.
C0G capacitors 1%, resistors 0.1%. Op-amp supply units: ANALOG_DECOUPLING.

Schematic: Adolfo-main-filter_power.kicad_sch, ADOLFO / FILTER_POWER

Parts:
C52, C53, C54, C55, C56, C57, C58, C59: 100nF 50V; c0805

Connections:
+12VA: C52.1, C54.1, C56.1, C58.1; also elsewhere on the board
-12VA: C53.1, C55.1, C57.1, C59.1; also elsewhere on the board
GND: C52.2, C53.2, C54.2, C55.2, C56.2, C57.2, C58.2, C59.2; also elsewhere on the board
